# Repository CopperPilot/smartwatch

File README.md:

# CopperPilot Rugged Smartwatch

**A rugged 49 mm smartwatch around an ESP32-S3 module, with a 1.9-inch IPS screen under flat cover glass, a rotary crown, side and action buttons, an optical heart-rate sensor in a domed back and magnetic rear charging, on a standard 49 mm sport band. Designed end to end by CopperPilot from three photos and a short prompt.**

> [!NOTE]
> **Designed by [CopperPilot](https://copperpilot.ai).** CopperPilot's agents designed every board, schematic, layout and enclosure part in this repo from one prompt and a few reference photos, then checked them with the gates and reviews below. Nobody edited the design files by hand. The prompt asked for a rugged smartwatch like the one in three photos, with the same bands, buttons, crown and display size, and heart-rate tracking, plus a short list of decisions (band type, rear charging, crown and button mechanics, bonded cover glass, domed back). The owner then asked for two review findings on the charging input to be fixed; the agents chose the parts, drew and routed the board, modelled the case and fixed every review finding themselves. **It has not been fabricated, assembled or powered on yet.** Everything here is open for review: if you see something a senior engineer would flag, [open an issue](../../issues/new/choose).

One 34 x 40 mm, 2-layer, 1.0 mm board with parts on both sides inside a 45 x 49 x 15 mm case:
- **Front:** a 1.9-inch 170 x 320 IPS panel (ST7789V2, SPI) under a flat cover glass bonded onto a ledge inside a
  1.8 mm raised rim.
- **Sides:** a rotary crown (a cap pressed onto a horizontal-shaft encoder through a sealed bore) and a side button
  on the right, an action button on the left; both buttons press side-actuated switches and clip in.
- **Back:** a domed, RF-transparent rear cover with an optical window over the MAX30102 heart-rate sensor and a
  2-pin magnetic pogo receptacle for the charging cable.
- **Band:** a bought 49 mm sport band slides sideways into lug channels at the top and bottom of the case.

## Status

### Done

- [x] Schematic: KiCad ERC, 0 errors
- [x] Layout: KiCad DRC with schematic parity and zone refill, 0 errors, 0 unconnected
- [x] Board rules no looser than the fab's limits, nothing silenced
- [x] Every part on the footprint and 3D model of its exact LCSC part
- [x] Every placed part has a live, in-stock LCSC/JLCPCB part number
- [x] High-speed groups (USB, MIPI, DDR where present) routed, length-matched, on target impedance
- [x] Every user-facing connector opens towards its case opening (checked on its 3D model)
- [x] Every connector mates from a known side, with a keep-clear zone KiCad DRC enforces
- [x] Both ends of every board-to-board cable carry the same signal on each wire
- [x] Datasheet-level design review: 0 P0 and 0 P1 findings open on every board
- [x] Enclosure parts are closed solids that fit the product envelope
- [x] Every enclosure part is manufacturable by its process (wall thickness, build size)
- [x] Full assembly with the real PCBAs: no collisions, seated or along any insertion path
- [x] Every cable joins two real connectors and fits its route in every pose
- [x] Every connector faces what mates with it; every screw hole sits on a boss
- [x] Every port opening has its connector right behind it
- [x] Every button and control physically reaches the switch it works
- [x] Every camera's whole field of view clears the case
- [x] Every part is held by something real (screw, snap, clip, adhesive, press fit)
- [x] Gerbers, drill, BOM and CPL exist and agree with the PCB
- [x] Independent judge (compares renders to the reference photos): **8/10** ([notes](reviews/judge.md))

### Pending

- [ ] Gate `sourcing.bom` warn: 32 extended parts (each adds a JLCPCB feeder fee); prefer basic parts where equivalent
- [ ] Gate `kicad.drc` warn: DRC warning silk_over_copper x23
- [ ] **Not built.** The board has not been fabricated or assembled and no case has been machined or printed.
- [ ] **No firmware.** The ESP32-S3 firmware (display, crown, buttons, heart rate, charging status) is not written or tested.
- [ ] **Bought parts are specified from drawings.** The 1.9-inch panel, the 220 mAh battery, the magnetic charging cable and the 49 mm band are modelled from typical listing drawings; exact suppliers still have to be chosen and checked against those models.
- [ ] **Judge notes (8/10):** the band lug channels are cut into flat end walls instead of blending into angled lug chamfers; the rectangular panel leaves a slightly wider black border than the reference display; the grille next to the action button is cosmetic (8 holes, no speaker on the board).
- [ ] **Water resistance not designed or tested.** The crown bore, button bores and bonded glass are sealed by design intent only; no gaskets are specified or rated.
- [ ] **DRC warnings:** 32 cosmetic warnings (silkscreen over copper or overlapping, and seven footprints that differ from their library copy); 0 errors.

0 P0 · 0 P1 · 0 P2 review findings open; the full reviews with evidence and suggested fixes are in [reviews/](reviews). Every P0 and P1 the reviews raised was fixed before release.

## Build film

[docs/build-film.mp4](docs/build-film.mp4) (48 s, 720p). Every part backs out along the direction it was fitted and goes back in assembly order, and every cable is drawn along its real route. Every frame is replayed against the 3D models (no part passes through another, the camera stays outside, the product stays in frame and faces you, no flicker), and a separate critic watches the film ([notes](reviews/film.md)).

## Renders

| | |
|:---:|:---:|
| <br>*Three-quarter view* | <br>*Front* |
| <br>*Rear* | <br>*Left side* |
| <br>*Right side* | <br>*Exploded* |
| <br>*Inside, top cover lifted away, every cable* | <br>*Inside from below, bottom cover lifted away* |
| <br>*Ports* | <br>*Buttons and controls, next to the parts they press* |

## What's inside

**Brain:** ESP32-S3-MINI-1 (Wi-Fi + Bluetooth LE, 8 MB flash) with a 32.768 kHz RTC crystal; its antenna sits
behind the non-metal rear cover.
**Power path:** magnetic pogo input → TVS clamp → 0.5 A hold / 1.0 A trip resettable fuse → reverse-polarity P-FET →
36 V overvoltage switch (ETA7014) → 6.5 V-rated current-limited, reverse-blocking switch (TPS2553) → MCP73832
charger for a 220 mAh 1S LiPo, with load sharing to the system rail. A TPS63031 buck-boost makes 3.3 V, an LDO makes
1.8 V for the heart-rate sensor, and a two-channel driver dims the backlight. A push-button reset controller resets
the MCU when the side button is held.

| Board | Size | Layers | Parts | Tracks | Vias | KiCad project | Review |
|---|---|---|---|---|---|---|---|
| Main board | 34 × 40 mm | 2 | 120 | 1,522 | 151 | [`hardware/rugged-smartwatch.kicad_pro`](hardware/rugged-smartwatch.kicad_pro) | [0 P0 · 0 P1](reviews/review-main.md) |

**Bought parts** (modelled from their drawings; the assembly checks use these models):

- **Display panel**: 1.9-inch 170x320 IPS TFT LCD display module with ST7789V2 4-wire SPI interface and 12-pin 0.5 mm pitch FPC tail (separate LEDA/LEDK backlight pins)
- **Battery**: 3.7 V 220 mAh 1S LiPo pouch battery (352022) with integrated protection PCB and 2-pin 1.0 mm JST-SH lead
- **Display psa**: Die-cut perimeter acrylic pressure-sensitive adhesive gasket bonding front cover glass to case ledge

## How it was made

CopperPilot's agents worked from the prompt in [reference/prompt.md](reference/prompt.md) and 3 reference photos ([reference/](reference)). The pipeline scopes the product into a written contract ([design/spec.yaml](design/spec.yaml)), designs the boards and the enclosure in parallel, integrates them, and only moves on when the gates pass. A separate review agent reads every board against the part datasheets, and a separate judge compares the result with the photos.

- Pipeline wall clock: about **37 h** over 10 launches (pipeline v98 to v127).

**Reference vs build:**

<sub>Reference photos of a commercial product, used here only for comparison. All rights belong to their owners; this project is not affiliated with or endorsed by the product's maker.</sub>

## Repository layout

```
hardware/          KiCad 10 projects (main board at the top, daughter boards in their own folders)
  lcsc.*, rea_refs.*   symbols, footprints and 3D models for every part, so the project opens anywhere
case/out/          enclosure parts (STL)
case/purchased/    bought parts used in the assembly checks
case/generate_case.py  the parametric enclosure source (uses CopperPilot's CAD helpers, not yet public)
fab/               Gerbers, drill, BOM, CPL, schematic PDF and STEP for each board; fab/mech/ enclosure STEP/STL
design/spec.yaml   the design contract the agents wrote and the gates check
reviews/           gate report, design reviews, the judge's notes, KiCad ERC/DRC
reference/         the prompt and the reference photos
docs/              build film and renders
```

## Manufacture

Every board targets **JLCPCB** standard PCB + assembly (1.0 mm FR-4); every part has an LCSC number. Per board: upload `*-gerbers.zip`, then `*-bom.csv` and `*-cpl.csv` for assembly, and check the part rotations in JLCPCB's preview before ordering.

The case body, crown cap, buttons and sensor window are designed for CNC (6061 aluminium, acrylic or sapphire for
the window), the rear cover for SLA in a ceramic-filled resin so the radio can see out; STEP files for each part are
in `fab/mech/`, with STLs for test prints. The board is set up for JLCPCB fabrication and two-sided assembly
(Gerbers, BOM and CPL).

> [!WARNING]
> This design has not been built yet. Fix or accept the open review findings above before you order boards, and expect a first revision to need changes.

## Review this design

Hardware gets better with more eyes on it. We'd like to hear what you'd flag:

- **Open an issue** ([design review template](../../issues/new/choose)) for a wrong pin, a missing part, a tight clearance, a part you'd swap, or a P1 above you disagree with.
- **Send a pull request** with a fix. Say which board and which reference designators it touches.
- **Build one** and tell us how it went: photos, bring-up notes and failures are all welcome.

Start with [reviews/](reviews): every finding has its evidence and a suggested fix.

## License

[CERN-OHL-S-2.0](LICENSE). You may use, study, modify, make and sell products from this design; modified versions must be shared under the same licence.

Part and product names are used only to say what fits; all trademarks belong to their owners.

<p align="center"><a href="https://copperpilot.ai"><b>Designed by CopperPilot</b></a>: we accelerate hardware design.<br><sub>More open designs: <a href="https://github.com/CopperPilot">github.com/CopperPilot</a></sub></p>

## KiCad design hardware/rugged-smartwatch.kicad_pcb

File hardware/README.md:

# Rugged 49 mm Smartwatch — Hardware & Electrical Design Documentation

Generated from `rea/spec.yaml` by `rea-hardware` (JLCPCB 2-layer stackup, 34.0 x 40.0 mm board outline at origin with 6.0 mm corner radius, and 4x M1.6 mounting holes), and completed with verified LCSC components, symbols, footprints, and 3D models.

## 1. Power Tree, Protection & Quiescent Current Budget

- **Rear Magnetic Pogo Charging Input (`J3`, `YZT0755-20028-02025-01`, LCSC `C5280828`, plus `TP9` on `/VCHG_RAW`):**
  - **Contact Current Rating:** Rated `2.0 A` per contact (`2 contacts` = `VCHG_RAW` and `GND`). Peak charging current is `147 mA` (`0.07x` rated current, `>13x` safety margin).
  - **ESD, Negative-Transient Clamping, Overcurrent PPTC Fuse, Reverse-Polarity Blocking, Overvoltage Protection & Reverse-Current Blocking:**
    - `D2` (`ESDLC12VLB`, YANGJIE 12 V bidirectional ESD/surge protection TVS diode in DFN1006-2L, LCSC `C20168169`, `V_RWM = 12 V`, `V_BR = 14.0 V` min, `V_C = 20 V` at `I_PP = 6 A` `< 24 V`, connected between `/VCHG_RAW` and `/GND`) provides IEC 61000-4-2 +/-30 kV bidirectional ESD and surge clamping. Because `V_C <= 20 V`, negative ESD or reverse-polarity transients on `J3.1` are clamped to `>= -20 V` (well inside upstream P-MOSFET `Q7` `AO3401A` `V_DS(max) = -30 V` when `Q7` is off and `C24` holds `VCHG_IN` at `0 V`), while positive transients are clamped to `<= +20 V` so `U6.1` (`OVP_FB`, via `R27 = 35.7 kOhm` / `R28 = 10.0 kOhm`) never exceeds `20 V * 10.0 / 45.7 = 4.38 V` (strictly below `U6`'s `+6.0 V` FB Absolute Maximum Rating). `R26` (`100 kOhm`) bleeds `VCHG_RAW` to `0.00 V` when unmated so exterior gold-plated contacts never carry DC bias against skin.
    - `F2` (`0603L050SLYR`, Littelfuse `0.50 A` hold / `1.00 A` trip ultra-low-resistance `0.14 Ohm` typ / `0.35 Ohm` max 0603 PPTC resettable fuse, LCSC `C207014`) sits in series with `J3.1` between `/VCHG_RAW` (`F2.1`) and `/VCHG_FUSED` (`F2.2`), tripping at `<= 1.00 A` (`>3.4x` margin above the `147 mA` normal charge current and `< 52 mV` voltage drop at `147 mA`) to protect `D1` (`PMEG2010EA,115`, `1.0 A` max) and `U8` (`TPS2553DBVR`, `1.5 A` max).
    - `Q7` (`AO3401A`, P-MOSFET in SOT-23, LCSC `C15127`, `V_DS(max) = -30 V`, `V_GS(max) = +/-12 V`, `R_DS(on) ~ 50 mOhm`, drain `Q7.3` on `/VCHG_FUSED`, source `Q7.2` on `/VCHG_IN`, gate `Q7.1` on `/VCHG_Q7_G`) blocks reverse-polarity connections on `J3` before they can reach `U6`'s `-0.3 V` substrate limit. `Q7`'s gate is pulled to `GND` by `R38 = 100 kOhm` (`0402WGF1003TCE`, LCSC `C25741`, providing full `V_GS = -5 V` gate drive during normal 5 V charging and dissipating `< 4 mW` at 20 V clamping) and clamped across Source-to-Gate by `D11` (`PESD5V0S1BL`, LCSC `C2912556`).
    - `C24` (`GRM188R6YA106MA73D`, 10 uF 35 V X5R 0603, LCSC `C194427`) provides high-voltage input decoupling on `/VCHG_IN` per `ETA7014S2G` datasheet recommendations.
    - `U6` (`ETA7014S2G`, 36 V input overvoltage protection load switch in SOT-23-6, LCSC `C7465500`, `R_ON = 35 mOhm` typ) sits on `/VCHG_IN` (`U6.4`, with `VCC`/`EN` `U6.5`/`U6.2` filtered via `R29 = 1 kOhm` `0402WGF1001TCE`, LCSC `C11702` + `C23 = 1 uF` 50 V X5R 0402 `GRM155R61H105KE05D`, LCSC `C1518208`) and outputs `/VCHG_PROT` (`U6.3`, bypassed by `C26 = 1 uF` 25 V X5R 0402 `CL05A105KA5NQNC`, LCSC `C52923`). Precision `0.1%` thin-film divider `R27 = 35.7 kOhm` (`ERA-2AEB3572X`, LCSC `C2075580`) and `R28 = 10.0 kOhm` (`RT0402BRD0710KL`, LCSC `C190095`) on `OVP_FB` (`U6.1`, `V_FB = 1.26 V +/- 0.05 V` = `1.21 V` min to `1.31 V` max) programs the overvoltage cutoff threshold to `V_OVP(typ) = 1.26 V * (35.7 + 10.0) / 10.0 = 5.758 V`, with worst-case minimum `V_OVP(min) = 1.21 V * (35.7 * 0.999 + 10.0 * 1.001) / (10.0 * 1.001) = 5.521 V > 5.500 V` (guaranteeing normal `4.75–5.50 V` USB `vSafe5V` input never trips OVP) and worst-case maximum `V_OVP(max) = 1.31 V * (35.7 * 1.001 + 10.0 * 0.999) / (10.0 * 0.999) = 5.996 V < 6.000 V` (strictly below the `6.5 V` recommended operating and `7.0 V` Absolute Maximum Rating of downstream `U8` `TPS2553DBVR`, and below the `6.0 V` recommended operating and `7.0 V` Absolute Maximum Rating of `U2` `MCP73832T-2ACI/OT`), while `U6`'s internal soft-start controls capacitive hot-plug inrush into `C26` (`1 uF`) and `C11` (`4.7 uF`).
    - `U8` (`TPS2553DBVR`, TI `2.5–6.5 V` recommended operating / `7.0 V` Absolute Maximum Rating, `1.5 A`, `85 mOhm` current-limited power-distribution switch with active reverse input-output voltage blocking in SOT-23-6, LCSC `C55266`) sits downstream of `U6` between `/VCHG_PROT` (`IN` Pin 1, tied to `EN` Pin 3) and `/VBUS` (`OUT` Pin 6, decoupled by `C11 = 4.7 uF`), providing `504 mV` of recommended-operating margin (`6.500 V` vs `V_OVP(max) = 5.996 V`) and `1.004 V` of absolute-maximum margin (`7.000 V` vs `5.996 V`) across `U6`'s entire OVP tolerance window, active reverse-voltage/reverse-current blocking (`I_rev = 0.01 uA` typ / `1.0 uA` max when `V_OUT > V_IN + 135 mV`) so no battery voltage back-feeds onto `/VCHG_PROT` or exposed pogo contact `J3.1`, and `2 us` fast electronic current limiting programmed via `R41 = 35.7 kOhm` `0.1%` (`ERA-2AEB3572X`, LCSC `C2075580`) on `ILIM` (Pin 5, net `/VCHG_ILIM`) to `I_OS(min) = 667 mA`, `I_OS(typ) = 729 mA`, `I_OS(max) = 799 mA < 1.0 A`.
    - Factory charging test pad `TP9` (`B.Cu`) is connected to `/VCHG_RAW` upstream of `F2`, `Q7`, `U6`, and `U8` so factory fixture supplies pass through full overcurrent, reverse-polarity, OVP, soft-start, and RCB protection.
- **Battery Connector (`J2`, `SM02B-SRSS-TB(LF)(SN)`, LCSC `C160402`), 12 V PPTC Fuse (`F1`) & UVLO-Wakeable Reverse-Battery Protection (`Q2` + `Q6` + `Q8` + `D10` + `D13` + `D12` + `R34..R37`):**
  - Connector entry `/VBAT_IN` (`J2.1`) is protected directly at the connector by `D9` (`PESD5V0S1BL`, 5 V bidirectional TVS diode, LCSC `C2912556`) and series resettable PPTC fuse `F1` (`ASMD0603SL100-12V`, 12 V, `1.0 A` hold / `2.0 A` trip ultra-low-resistance `45 mOhm` typ 0603 PPTC fuse, LCSC `C48783158`).
  - High-side reverse-polarity P-MOSFET `Q2` (`AO3401A`, LCSC `C15127`, drain on `/VBAT_FUSED`, source on `/VBAT`) has its gate (`/VBAT_Q2_G`) pulled to its source (`/VBAT`) via `R34 = 1 MOhm` (`0402WGF1004TCE`, LCSC `C26083`) and pulled to `/GND` by N-MOSFET `Q6` (`BSS138K`, LCSC `C5224263`, `V_GS(th) = 0.4–1.0 V`), whose gate (`/VBAT_Q2_EN`) is driven from `/VBAT_FUSED` via `R35 = 100 kOhm` (`0402WGF1003TCE`, LCSC `C25741`) and from `/VBUS` via ultra-low-leakage diode `D10` (`1N4148WS`, LCSC `C2128`, net `/VBAT_WAKE`) in series with `R36 = 100 kOhm` (`0402WGF1003TCE`, LCSC `C25741`), while a second blocking diode `D13` (`1N4148WS`, LCSC `C2128`, net `/VBAT_SENSE_WAKE`) separately feeds `R37 = 100 kOhm` (`0402WGF1003TCE`, LCSC `C25741`), NPN BJT `Q8` (`MMBT3904`, LCSC `C909754`), and Schottky diode `D12` (`1N5819WS`, LCSC `C191023`) for reverse-polarity lockout without bleeding battery current (`0 uA` parasitic path from `VBAT_FUSED` through `R35 -> R36` when unplugged, preserving full `V_GS(Q6) = 3.0–4.2 V` gate drive).
- **1S LiPo Linear Charger (`U2`, `MCP73832T-2ACI/OT`, LCSC `C38066`) & Digital VBUS Detection (`R24`/`R25`):**
  - `R10 = 6.8 kOhm` (`C25917`) programs `I_REG = 1000 V / 6.8 kOhm = 147.1 mA` (`0.67C` for the `220 mAh` `LP352022` pouch cell).
  - Open-drain charge status output `U2.1` (`STAT`) is pulled up to `+3V3` via `R23` (`10 kOhm`) and routed to `U1.14` (`IO10`, `CHG_STAT`).
  - `/VBUS` presence is sensed digitally on `U1.15` (`GPIO11` / `RTC_GPIO11`) via `R24 = 68 kOhm` (`0402WGF6802TCE`, `C36871`) and `R25 = 100 kOhm` (`0402WGF1003TCE`, `C25741`), yielding `2.77–3.15 V > V_IH(min) = 2.475 V`.
- **Load-Sharing Power Path (`Q1` `AO3401A` + `D1` `PMEG2010EA,115` + `R13` `1 kOhm`), Buck-Boost +3V3 Regulation (`U4` `TPS63031DSKR` + `L1` `1.5 uH`) & LDO +1V8 Regulation (`U5` `ME6211C18M5G-N`):**
  - Low-leakage MEGA Schottky `D1` (`PMEG2010EA,115`, LCSC `C193668`) and P-MOSFET `Q1` (`AO3401A`, LCSC `C15127`, with `1 kOhm` gate pulldown `R13`) provide automatic single-diode-drop power path switching onto `/VSYS` (`10 uF` `C7`).
  - `U4` (`TPS63031DSKR`, LCSC `C15516`, `1.8–5.5 V` input, `3.3 V` fixed output buck-boost converter with `1.5 uH` inductor `L1` `WPN201610U1R5MT`, LCSC `C97017`, `EN` and `PS/SYNC` `U4.6`/`U4.7` tied to `VINA`/`VIN` on `/VSYS`, dedicated `100 nF` `C28` on `VINA` `U4.8`, `100 nF` `C3` adjacent to `U4.1` `VOUT`, and two parallel `10 uF` 25 V X5R 0603 bulk capacitors `C8` + `C27` `CL10A106MA8NRNC` `C96446` providing `>= 12 uF` DC-biased effective output capacitance) maintains regulated `+3V3` across the full `3.0–4.2 V` 1S LiPo discharge range, and `U5` (`ME6211C18M5G-N`, `C236671`, `1.8 V / 300 mA` LDO, `CE` tied to `VSYS`) supplies continuous `+1V8` to `U3` (`MAX30102EFD+T` `VDD`).
  - **Local IC Decoupling on `/+3V3`:** `C1` (`100 nF` 0402, `C1525`, at `8.29, 3.85 mm`) and `C13` (`10 uF` 0603, `C96446`, at `8.38, 5.85 mm`) are functionally grouped in the schematic and placed within `1.54–1.97 mm` of `U1` pin 3 (`3V3` pad at `10.02, 4.75 mm`) on `F.Cu` with dedicated local `/GND` stitching vias (`7.20, 3.85 mm` and `7.20, 6.625 mm`); `C4` (`100 nF` 0402, `C1525`, at `30.10, 23.45 mm`) is functionally grouped and placed immediately adjacent (`0.77 mm`) to `U9` (`TPS3421EGDRYR` at `31.25, 23.80 mm`) pin 4 (`VCC` pad at `30.86, 23.30 mm`) with a dedicated `/GND` stitching via at `(29.65, 23.65 mm)`.

## 2. Display Backlight Constant-Current Driver, UI Protection & Sensor Level Shifting

- **Display FPC (`J1`, `FPC-05FB-12PH20`, LCSC `C2856829`) & Constant-Current Backlight Driver (`U7`, `CAT4002ASD-GT3`, LCSC `C890382`):**
  - 12-pin 0.5 mm pitch double-sided contact FPC connector `J1` mates with the 12-pin 1.9-inch `170x320` `ST7789V2` IPS TFT module (`ZJY190S0800TG01` / `GMT169-01`), with `100 kOhm` pull-ups `R39`/`R40` on `LCD_CS`/`LCD_RES`, separate `LEDA` (Pin 3, tied to `/VSYS` with `1 uF` bypass `C25`), and `LEDK` (Pin 2, `/LCD_LEDK`) regulated by `U7` (`CAT4002ASD-GT3`, `R14 = 3.6 kOhm` for `41.7 mA` total sink current, dimmed via 1-wire EZDim pulse bursts on `U7.1` from `U1.25`).
- **Sealed-Enclosure Long-Press Push-Button Hardware Reset Supervisor (`U9`, `TPS3421EGDRYR`, LCSC `C2067262`):**
  - `U9` (`TPS3421EGDRYR`, `250 nA` push-button reset controller in SON-6, `TS` tied to `/GND` for `7.5 s` setup delay) monitors `SW2` (`/BTN_SIDE_SW`) and asserts a `400 ms` active-low hardware reset pulse on `/MCU_EN` (`U1.45`) when `SW2` is held for `>= 7.5 s`.
- **Rotary Encoder (`SW1`, `EC05E1220203`) & Tactile Button (`SW2`/`SW3`, `SKRTLAE010`) Contact-Current & ESD Protection:**
  - Switch terminals have `10 kOhm` pull-ups `R3..R6` to `+3V3` and 5 V bidirectional ESD TVS diodes `D5..D8` (`PESD5V0S1BL`, LCSC `C2912556`), followed by `10 kOhm` series current-limiting/ESD-isolation resistors `R30..R33` feeding `10 nF` encoder filter capacitors `C17..C18` (`<= 0.33 mA` contact discharge current) and `100 nF` tactile switch debounce capacitors `C19..C20`.
- **1.8 V <-> 3.3 V Fast-Mode I2C & Interrupt Level Translation (`Q3..Q5`, `BSS138K`, LCSC `C5224263`):**
  - `Q3`, `Q4`, and `Q5` use low-capacitance sub-1V-threshold small-signal N-MOSFETs (`BSS138K`, `C_iss = 25 pF`, `C_oss = 9.7 pF`, `C_rss = 2.2 pF`, `V_GS(th) = 0.4–1.0 V`) with gates on `+1V8`, `1.8 kOhm` pull-ups `R7, R8` (to `+1V8`) and `R20, R21` (to `+3V3`, `0402WGF1801TCE`, LCSC `C25871`) on `I2C_SCL` and `I2C_SDA` (yielding RC rise time `t_r ~ 70 ns << 300 ns` 400 kHz Fast-Mode limit while keeping total low-level sink current `I_OL = 2.83 mA < 3.0 mA`), and `10 kOhm` pull-ups `R9` (to `+1V8`) and `R22` (to `+3V3`, `0402WGF1002TCE`, LCSC `C25744`) on open-drain interrupt `HR_INT`.

## 3. Datasheet Derating Summary (Capacitors, MOSFETs, Connectors & Bootloader Path)

- **Capacitor Voltage Ratings (`>= 1.5x` Maximum Net Voltage):**
  - `/OVP_VCC` (`<= 20 V` surge clamped by `D2`): `C23` (`1 uF`, `GRM155R61H105KE05D`, `C1518208`) rated `50 V` (`2.50x` surge / `10.0x` nominal 5 V).
  - `/VCHG_IN` (`<= 20 V` surge clamped by `D2`): `C24` (`10 uF`, `GRM188R6YA106MA73D`, `C194427`) rated `35 V` (`1.75x` surge / `7.0x` nominal 5 V).
  - `/VCHG_PROT` (`<= 5.996 V` `U6` OVP cutoff): `C26` (`1 uF`, `CL05A105KA5NQNC`, `C52923`) rated `25 V` (`4.17x`).
  - `/VBUS` (`<= 5.996 V` OVP cutoff): `C11` (`4.7 uF`, `CL10A475KO8NNNC`, `C19666`) rated `16 V` (`2.67x`).
  - `/VBAT` (`<= 4.20 V` LiPo charge voltage): `C12` (`4.7 uF`, `CL10A475KO8NNNC`, `C19666`) rated `16 V` (`3.81x`).
  - `/VSYS` (`<= 5.8 V` OVP / `4.6 V` nominal): `C7, C14` (`10 uF`, `25 V`, `C96446`), `C25` (`1 uF`, `25 V`, `C52923`), and `C6, C28` (`100 nF`, `16 V`, `C1525`) provide `>= 2.76x` margin.
  - `/+3V3`, `/+1V8`, `/VBAT_ADC`, `/MCU_EN`, UI & RTC crystal nets (`<= 3.3 V`): `C1..C5, C15, C19, C20` (`16 V`), `C8, C9, C10, C13, C27` (`25 V`), and `C17, C18, C21, C22` (`50 V`) provide `>= 4.85x` margin.
- **MOSFET `|V_GS|` and `|V_DS|` Ratings:**
  - `Q7` (`AO3401A`, `V_DS(max) = -30 V`, `V_GS(max) = +/-12 V`): upstream `D2` (`ESDLC12VLB`, `V_C = 20 V` at `6 A`) clamps `|V_DS| <= 20 V < 30 V`, and `D11` (`PESD5V0S1BL` across Source-to-Gate) clamps `|V_GS| <= 7.0 V < 12 V`.
  - `Q1, Q2` (`AO3401A`, `V_DS(max) = -30 V`, `V_GS(max) = +/-12 V`): operate on `/VBUS` (`<= 6.0 V`) and `/VBAT` (`<= 4.2 V`), keeping `|V_GS| <= 6.0 V < 12 V` and `|V_DS| <= 6.0 V < 30 V`.
  - `Q3..Q6` (`BSS138K`, `V_DS(max) = 60 V`, `V_GS(max) = +/-20 V`): operate on `1.8 V`, `3.3 V`, and `4.2 V` nets (`|V_GS| <= 4.2 V < 20 V`).
- **Connector Contact Current Ratings & Ground Returns:**
  - `J3` (`YZT0755-20028-02025-01`, 2-pin pogo): rated `2.0 A`/contact vs `147 mA` charge current (`13.6x` margin).
  - `J2` (`SM02B-SRSS-TB(LF)(SN)`, 2-pin JST-SH): rated `1.0 A`/contact vs `<= 365 mA` peak battery current (`2.74x` margin).
  - `J1` (`FPC-05FB-12PH20`, 12-pin 0.5 mm FPC): rated `0.5 A`/contact vs `41.7 mA` on `LEDA`/`LEDK` and `< 15 mA` on `+3V3` `VDD`, with 4 distributed `GND` return pins (`Pins 1, 5, 6, 12`) flanking the backlight and 4-wire SPI signals.
- **MCU Programming & Bootloader Conditions (`U1`, `ESP32-S3-MINI-1-N8`):**
  - Native USB Serial/JTAG (`GPIO19` `USB_D-` / `GPIO20` `USB_D+` via `22 Ohm` `R15`/`R16` and `PESD5V0U1BL` `D3`/`D4`) and `UART0` (`U0TXD`/`U0RXD`), `MCU_EN` (`R1 = 10 kOhm` pull-up to `+3V3`, `C10 = 1 uF` delay, `TP6`), `GPIO0` (`BOOT_IO0`, `R2 = 10 kOhm` pull-up to `+3V3`, `TP5`), `+3V3` (`TP8`), `VCHG_RAW` (`TP9`), and `GND` (`TP7`) are exposed on `B.Cu` pogo test pads `TP1..TP9` (`GPIO45` and `GPIO46` strapping pins left unconnected at default internal pull-down).

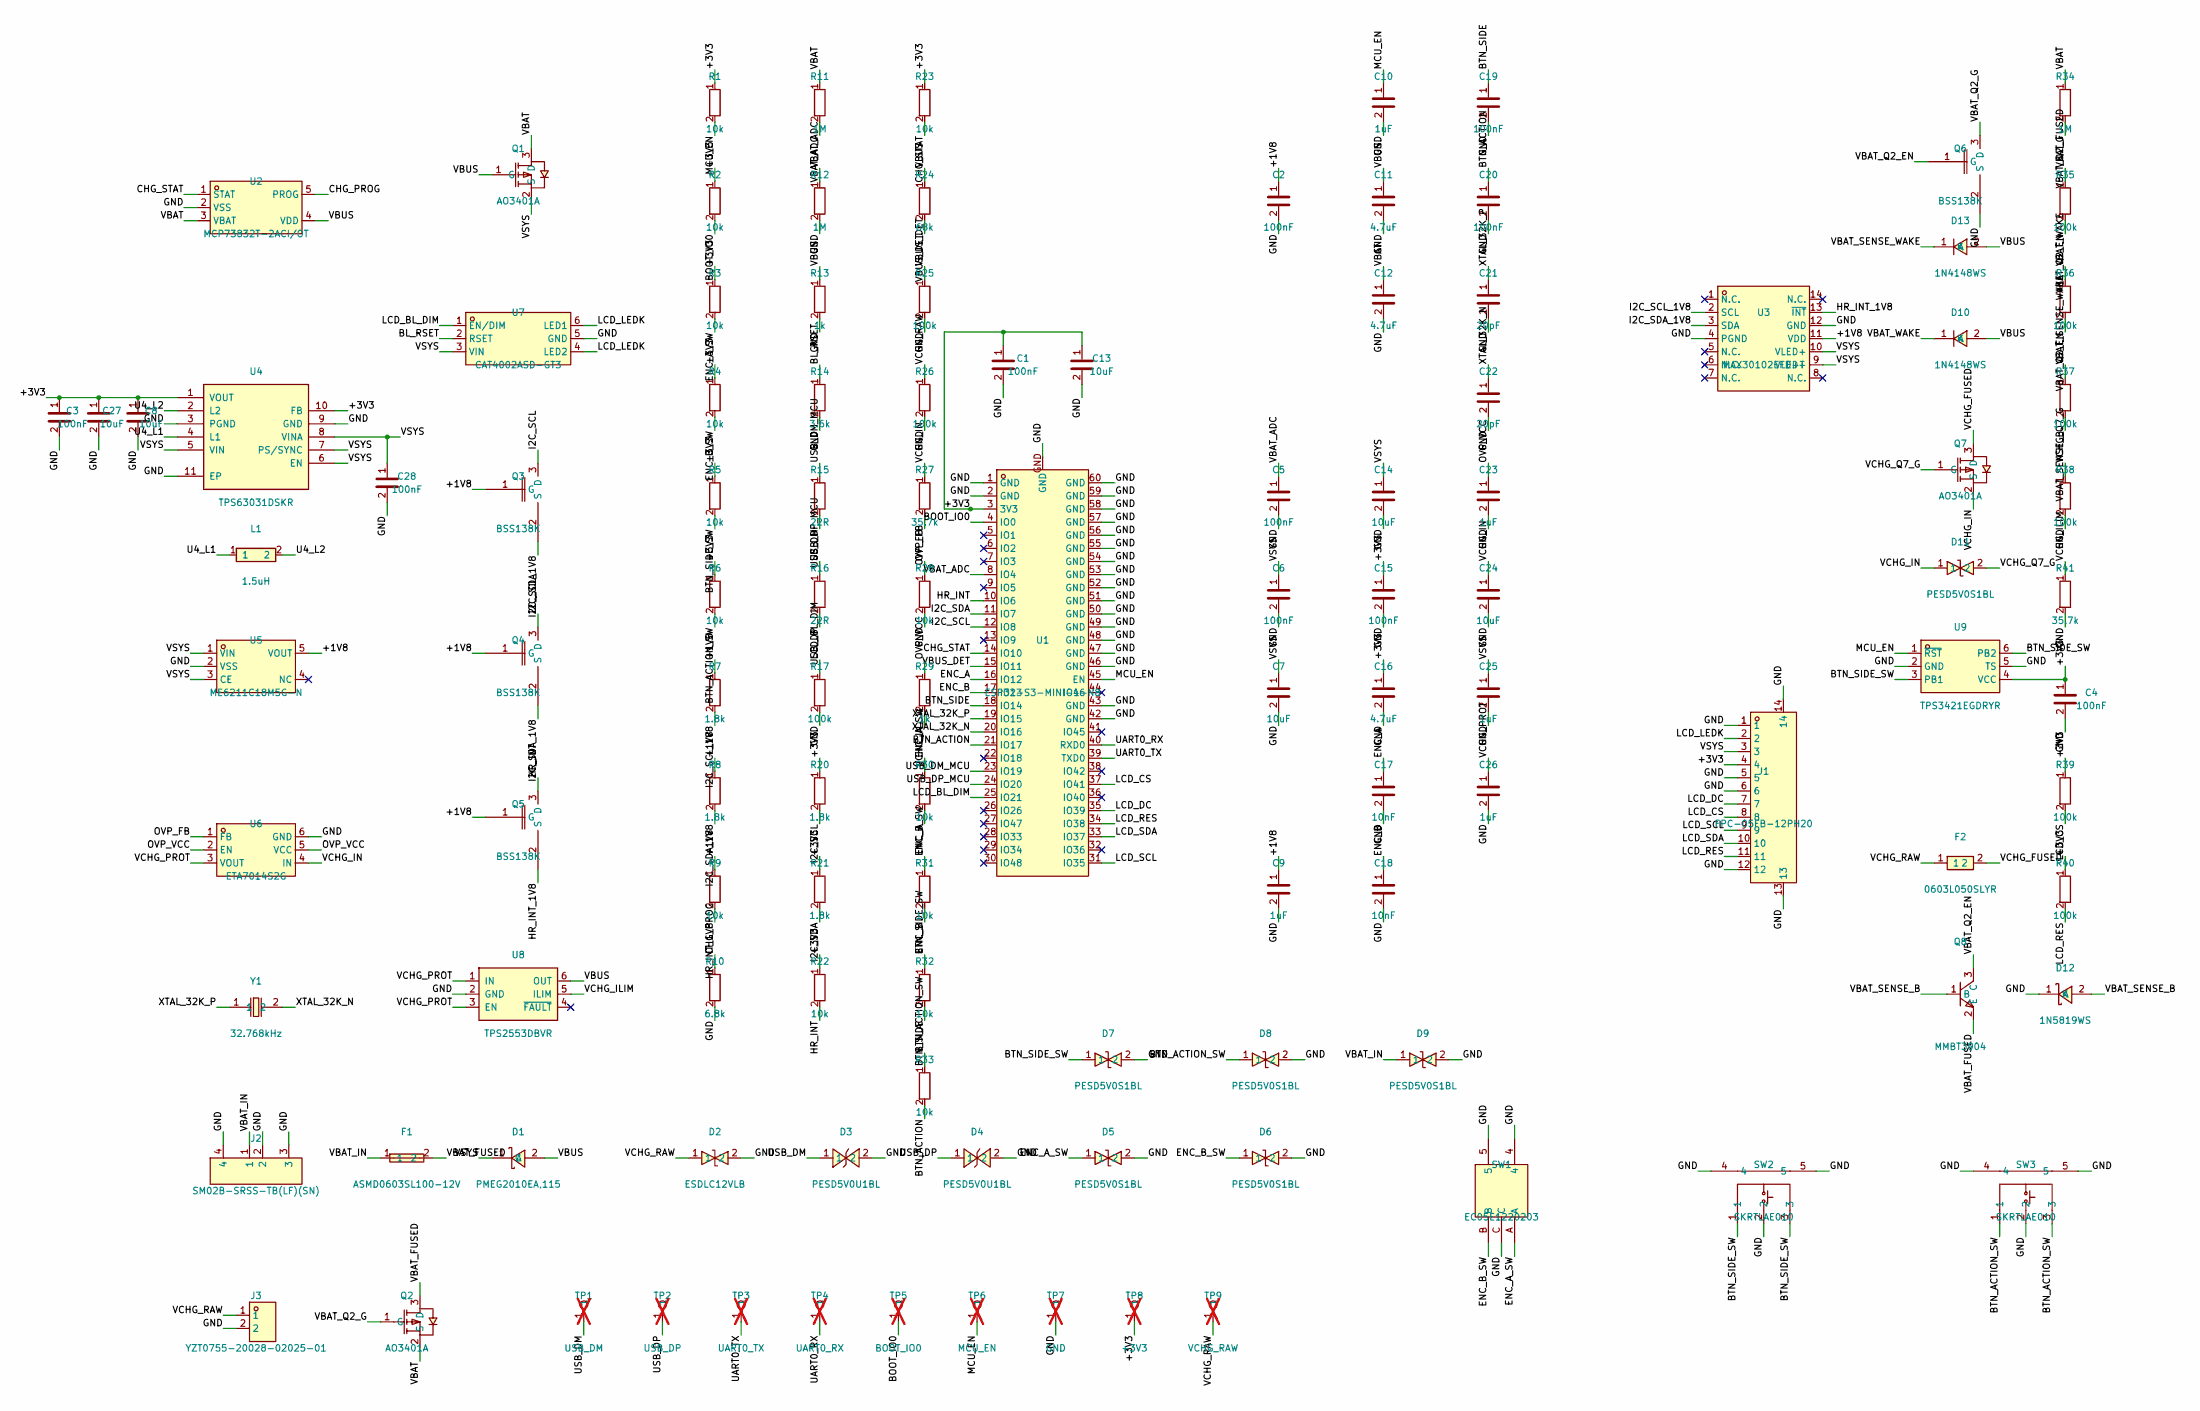
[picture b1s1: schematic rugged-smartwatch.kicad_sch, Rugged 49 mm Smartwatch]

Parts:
C1, C2, C3, C4, C5, C6, C15, C19, C20, C28: 100nF; C_0402_1005Metric; MPN CL05B104KO5NNNC; LCSC C1525
C7, C8, C13, C14, C27: 10uF; C_0603_1608Metric; MPN CL10A106MA8NRNC; LCSC C96446
C9, C10, C25, C26: 1uF; C_0402_1005Metric; MPN CL05A105KA5NQNC; LCSC C52923
C11, C12, C16: 4.7uF; C_0603_1608Metric; MPN CL10A475KO8NNNC; LCSC C19666
C17, C18: 10nF; C_0402_1005Metric; MPN CC0402KRX7R9BB103; LCSC C60133
C21, C22: 20pF; C_0402_1005Metric; MPN 0402CG200J500NT; LCSC C1554
C23: 1uF; C_0402_1005Metric; MPN GRM155R61H105KE05D; LCSC C1518208
C24: 10uF; C_0603_1608Metric; MPN GRM188R6YA106MA73D; LCSC C194427
D1: PMEG2010EA,115; SOD-323_L1.8-W1.3-LS2.5-RD; MPN PMEG2010EA,115; LCSC C193668
D2: ESDLC12VLB; DFN1006-2L-BI; MPN ESDLC12VLB; LCSC C20168169
D3, D4: PESD5V0U1BL; SOD-882_L1.0-W0.6-BI-1; MPN PESD5V0U1BL; LCSC C2827663
D5, D6, D7, D8, D9, D11: PESD5V0S1BL; DFN1006-2L-BI-1; MPN PESD5V0S1BL; LCSC C2912556
D10, D13: 1N4148WS; SOD-323_L1.8-W1.3-LS2.5-RD; MPN 1N4148WS; LCSC C2128
D12: 1N5819WS; SOD-323_L1.8-W1.3-LS2.5-RD; MPN 1N5819WS; LCSC C191023
F1: ASMD0603SL100-12V; F0603; MPN ASMD0603SL100-12V; LCSC C48783158
F2: 0603L050SLYR; F0603; MPN 0603L050SLYR; LCSC C207014
J1: FPC-05FB-12PH20; FPC-SMD_12P-P0.50_XUNPU_FPC-05FB-12PH20; MPN FPC-05FB-12PH20; LCSC C2856829
J2: SM02B-SRSS-TB(LF)(SN); CONN-SMD_2P-P1.00_SM02B-SRSS-TB-LF-SN; MPN SM02B-SRSS-TB(LF)(SN); LCSC C160402
J3: YZT0755-20028-02025-01; CONN-SMD_YZT0755-20028-02025-01; MPN YZT0755-20028-02025-01; LCSC C5280828
L1: 1.5uH; IND-SMD_L2.0-W1.6; MPN WPN201610U1R5MT; LCSC C97017
Q1, Q2, Q7: AO3401A; SOT-23_L2.9-W1.3-P1.90-LS2.4-BR; MPN AO3401A; LCSC C15127
Q3, Q4, Q5, Q6: BSS138K; SOT-23-3_L2.9-W1.3-P1.90-LS2.4-BR; MPN BSS138K; LCSC C5224263
Q8: MMBT3904; SOT-23-3_L2.9-W1.3-P1.90-LS2.4-BR; MPN MMBT3904; LCSC C909754
R1, R2, R3, R4, R5, R6, R9, R22, R23, R30, R31, R32, R33: 10k; R_0402_1005Metric; MPN 0402WGF1002TCE; LCSC C25744
R7, R8, R20, R21: 1.8k; R_0402_1005Metric; MPN 0402WGF1801TCE; LCSC C25871
R10: 6.8k; R_0402_1005Metric; MPN 0402WGF6801TCE; LCSC C25917
R11, R12, R34: 1M; R_0402_1005Metric; MPN 0402WGF1004TCE; LCSC C26083
R13, R29: 1k; R_0402_1005Metric; MPN 0402WGF1001TCE; LCSC C11702
R14: 3.6k; R_0402_1005Metric; MPN 0402WGF3601TCE; LCSC C25891
R15, R16: 22R; R_0402_1005Metric; MPN 0402WGF220JTCE; LCSC C25092
R17, R25, R26, R35, R36, R37, R38, R39, R40: 100k; R_0402_1005Metric; MPN 0402WGF1003TCE; LCSC C25741
R24: 68k; R_0402_1005Metric; MPN 0402WGF6802TCE; LCSC C36871
R27, R41: 35.7k; R_0402_1005Metric; MPN ERA-2AEB3572X; LCSC C2075580
R28: 10k; R_0402_1005Metric; MPN RT0402BRD0710KL; LCSC C190095
SW1: EC05E1220203; SW-SMD_EC05E1220203; MPN EC05E1220203; LCSC C390930
SW2, SW3: SKRTLAE010; KEY-SMD_SKRTLAE010; MPN SKRTLAE010; LCSC C110293
TP1: USB_DM; TestPoint_Pad_D1.0mm; not fitted
TP2: USB_DP; TestPoint_Pad_D1.0mm; not fitted
TP3: UART0_TX; TestPoint_Pad_D1.0mm; not fitted
TP4: UART0_RX; TestPoint_Pad_D1.0mm; not fitted
TP5: BOOT_IO0; TestPoint_Pad_D1.0mm; not fitted
TP6: MCU_EN; TestPoint_Pad_D1.0mm; not fitted
TP7: GND; TestPoint_Pad_D1.0mm; not fitted
TP8: +3V3; TestPoint_Pad_D1.0mm; not fitted
TP9: VCHG_RAW; TestPoint_Pad_D1.0mm; not fitted
U1: ESP32-S3-MINI-1-N8; BULETM-SMD_ESP32-S3-MINI-1-N8; MPN ESP32-S3-MINI-1-N8; LCSC C2913206
U2: MCP73832T-2ACI/OT; SOT-23-5_L3.0-W1.7-P0.95-LS2.8-BL; MPN MCP73832T-2ACI/OT; LCSC C38066
U3: MAX30102EFD+T; OESIP-14_L5.6-W3.3-P0.80-TL; MPN MAX30102EFD+T; LCSC C6454833
U4: TPS63031DSKR; SON-10_L2.5-W2.5-P0.50-TL-EP; MPN TPS63031DSKR; LCSC C15516
U5: ME6211C18M5G-N; SOT-23-5_L3.0-W1.7-P0.95-LS2.8-BR; MPN ME6211C18M5G-N; LCSC C236671
U6: ETA7014S2G; SOT-23-6_L2.9-W1.6-P0.95-LS2.8-BL; MPN ETA7014S2G; LCSC C7465500
U7: CAT4002ASD-GT3; SC-70-6_L2.0-W1.3-P0.65-LS2.1-BR; MPN CAT4002ASD-GT3; LCSC C890382
U8: TPS2553DBVR; SOT-23-6_L2.9-W1.6-P0.95-LS2.8-BR; MPN TPS2553DBVR; LCSC C55266
U9: TPS3421EGDRYR; SON-6_L1.5-W1.0-P0.50-BL; MPN TPS3421EGDRYR; LCSC C2067262
Y1: 32.768kHz; FC-135R_L3.2-W1.5; MPN Q13FC13500004; LCSC C32346

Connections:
/+1V8: C2.1, C9.1, Q3.1 (G), Q4.1 (G), Q5.1 (G), R7.1, R8.1, R9.1, U3.11 (VDD), U5.5 (VOUT)
/+3V3: C1.1, C3.1, C4.1, C8.1, C13.1, C15.1, C16.1, C27.1, J1.4, R1.1, R2.1, R3.1, R4.1, R5.1, R6.1, R20.1, R21.1, R22.1, R23.1, R39.1, R40.1, TP8.1, U1.3 (3V3), U4.1 (VOUT), U4.10 (FB), U9.4 (VCC)
/BL_RSET: R14.1, U7.2 (RSET)
/BOOT_IO0: R2.2, TP5.1, U1.4 (IO0)
/BTN_ACTION: C20.1, R33.2, U1.21 (IO17)
/BTN_ACTION_SW: D8.1, R6.2, R33.1, SW3.1, SW3.3
/BTN_SIDE: C19.1, R32.2, U1.18 (IO14)
/BTN_SIDE_SW: D7.1, R5.2, R32.1, SW2.1, SW2.3, U9.3 (PB1), U9.6 (PB2)
/CHG_PROG: R10.1, U2.5 (PROG)
/CHG_STAT: R23.2, U1.14 (IO10), U2.1 (STAT)
/ENC_A: C17.1, R30.2, U1.16 (IO12)
/ENC_A_SW: D5.1, R3.2, R30.1, SW1.A
/ENC_B: C18.1, R31.2, U1.17 (IO13)
/ENC_B_SW: D6.1, R4.2, R31.1, SW1.B
/GND: C1.2, C2.2, C3.2, C4.2, C5.2, C6.2, C7.2, C8.2, C9.2, C10.2, C11.2, C12.2, C13.2, C14.2, C15.2, C16.2, C17.2, C18.2, C19.2, C20.2, C21.2, C22.2, C23.2, C24.2, C25.2, C26.2, C27.2, C28.2, D2.2, D3.2, D4.2, D5.2, D6.2, D7.2, D8.2, D9.2, D12.1 (K), J1.1, J1.5, J1.6, J1.12, J1.13, J1.14, J2.2, J2.3, J2.4, J3.2, Q6.2 (S), R10.2, R12.2, R13.2, R14.2, R17.2, R25.2, R26.2, R28.2, R38.2, R41.2, SW1.4, SW1.5, SW1.C, SW2.2, SW2.4, SW2.5, SW3.2, SW3.4, SW3.5, TP7.1, U1.1 (GND), U1.2 (GND), U1.42 (GND), U1.43 (GND), U1.46 (GND), U1.47 (GND), U1.48 (GND), U1.49 (GND), U1.50 (GND), U1.51 (GND), U1.52 (GND), U1.53 (GND), U1.54 (GND), U1.55 (GND), U1.56 (GND), U1.57 (GND), U1.58 (GND), U1.59 (GND), U1.60 (GND), U1.GND, U2.2 (VSS), U3.4 (PGND), U3.12 (GND), U4.3 (PGND), U4.9 (GND), U4.11 (EP), U5.2 (VSS), U6.6 (GND), U7.5 (GND), U8.2 (GND), U9.2 (GND), U9.5 (TS)
/HR_INT: Q5.3 (D), R22.2, U1.10 (IO6)
/HR_INT_1V8: Q5.2 (S), R9.2, U3.13 (~INT)
/I2C_SCL: Q3.3 (D), R20.2, U1.12 (IO8)
/I2C_SCL_1V8: Q3.2 (S), R7.2, U3.2 (SCL)
/I2C_SDA: Q4.3 (D), R21.2, U1.11 (IO7)
/I2C_SDA_1V8: Q4.2 (S), R8.2, U3.3 (SDA)
/LCD_BL_DIM: R17.1, U1.25 (IO21), U7.1 (EN/DIM)
/LCD_CS: J1.8, R39.2, U1.37 (IO41)
/LCD_DC: J1.7, U1.35 (IO39)
/LCD_LEDK: J1.2, U7.4 (LED2), U7.6 (LED1)
/LCD_RES: J1.11, R40.2, U1.34 (IO38)
/LCD_SCL: J1.9, U1.31 (IO35)
/LCD_SDA: J1.10, U1.33 (IO37)
/MCU_EN: C10.1, R1.2, TP6.1, U1.45 (EN), U9.1 (~RST)
/OVP_FB: R27.2, R28.1, U6.1 (FB)
/OVP_VCC: C23.1, R29.1, U6.2 (EN), U6.5 (VCC)
/U4_L1: L1.1, U4.4 (L1)
/U4_L2: L1.2, U4.2 (L2)
/UART0_RX: TP4.1, U1.40 (RXD0)
/UART0_TX: TP3.1, U1.39 (TXD0)
/USB_DM: D3.1, R15.2, TP1.1
/USB_DM_MCU: R15.1, U1.23 (IO19)
/USB_DP: D4.1, R16.2, TP2.1
/USB_DP_MCU: R16.1, U1.24 (IO20)
/VBAT: C12.1, Q1.3 (D), Q2.2 (S), R11.1, R34.1, U2.3 (VBAT)
/VBAT_ADC: C5.1, R11.2, R12.1, U1.8 (IO4)
/VBAT_FUSED: F1.2, Q2.3 (D), Q8.2 (E), R35.1
/VBAT_IN: D9.1, F1.1, J2.1
/VBAT_Q2_EN: Q6.1 (G), Q8.3 (C), R35.2, R36.2
/VBAT_Q2_G: Q2.1 (G), Q6.3 (D), R34.2
/VBAT_SENSE_B: D12.2 (A), Q8.1 (B), R37.2
/VBAT_SENSE_WAKE: D13.1 (K), R37.1
/VBAT_WAKE: D10.1 (K), R36.1
/VBUS: C11.1, D1.2 (A), D10.2 (A), D13.2 (A), Q1.1 (G), R13.1, R24.1, U2.4 (VDD), U8.6 (OUT)
/VBUS_DET: R24.2, R25.1, U1.15 (IO11)
/VCHG_FUSED: F2.2, Q7.3 (D)
/VCHG_ILIM: R41.1, U8.5 (ILIM)
/VCHG_IN: C24.1, D11.1, Q7.2 (S), R27.1, R29.2, U6.4 (IN)
/VCHG_PROT: C26.1, U6.3 (VOUT), U8.1 (IN), U8.3 (EN)
/VCHG_Q7_G: D11.2, Q7.1 (G), R38.1
/VCHG_RAW: D2.1, F2.1, J3.1, R26.1, TP9.1
/VSYS: C6.1, C7.1, C14.1, C25.1, C28.1, D1.1 (C), J1.3, Q1.2 (S), U3.9 (VLED+), U3.10 (VLED+), U4.5 (VIN), U4.6 (EN), U4.7 (PS/SYNC), U4.8 (VINA), U5.1 (VIN), U5.3 (CE), U7.3 (VIN)
/XTAL_32K_N: C22.1, U1.20 (IO16), Y1.2
/XTAL_32K_P: C21.1, U1.19 (IO15), Y1.1

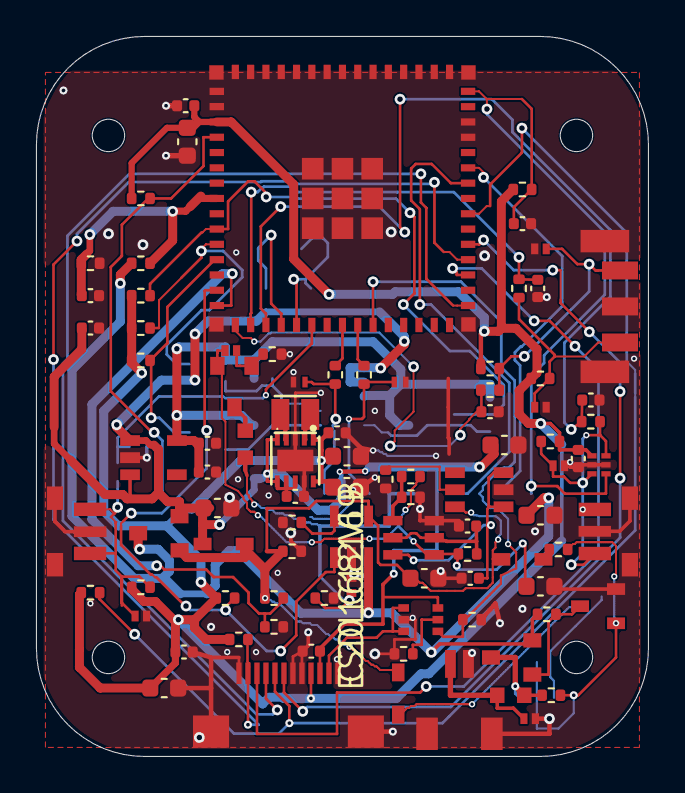
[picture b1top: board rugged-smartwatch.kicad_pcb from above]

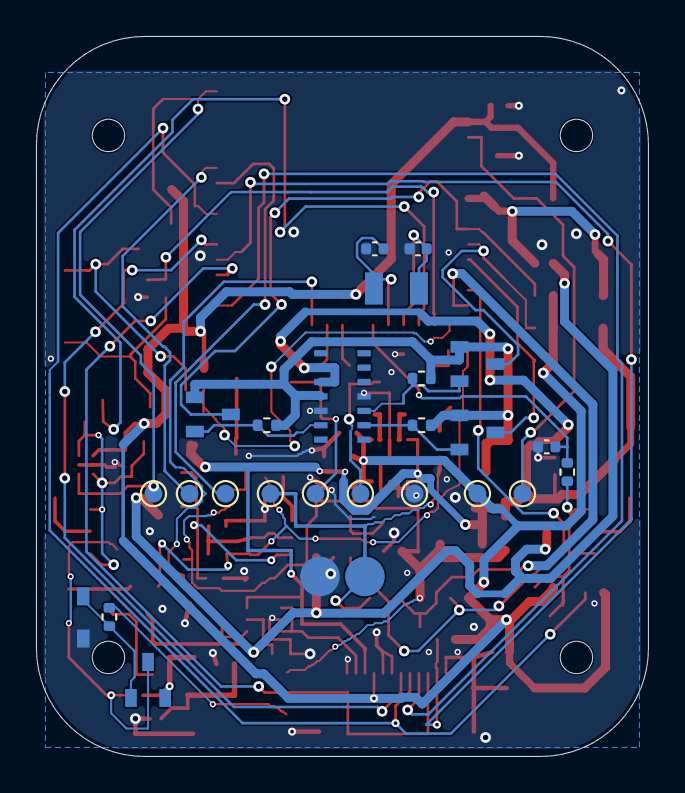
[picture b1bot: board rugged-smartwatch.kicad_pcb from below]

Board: 2 copper layers, 34.0 x 40.0 mm, 120 parts (25 on the bottom side), 59 nets.

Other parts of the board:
H1, H2, H3, H4: MountingHole; MountingHole_1.8mm

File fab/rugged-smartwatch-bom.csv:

Comment,Designator,Footprint,LCSC Part #
100nF,"C1,C2,C3,C4,C5,C6,C15,C19,C20,C28",C_0402_1005Metric,C1525
1uF,"C9,C10,C25,C26",C_0402_1005Metric,C52923
4.7uF,"C11,C12,C16",C_0603_1608Metric,C19666
10uF,"C7,C8,C13,C14,C27",C_0603_1608Metric,C96446
10nF,"C17,C18",C_0402_1005Metric,C60133
20pF,"C21,C22",C_0402_1005Metric,C1554
1uF,C23,C_0402_1005Metric,C1518208
10uF,C24,C_0603_1608Metric,C194427
"PMEG2010EA,115",D1,SOD-323_L1.8-W1.3-LS2.5-RD,C193668
1N4148WS,"D10,D13",SOD-323_L1.8-W1.3-LS2.5-RD,C2128
PESD5V0S1BL,"D5,D6,D7,D8,D9,D11",DFN1006-2L-BI-1,C2912556
1N5819WS,D12,SOD-323_L1.8-W1.3-LS2.5-RD,C191023
ESDLC12VLB,D2,DFN1006-2L-BI,C20168169
PESD5V0U1BL,"D3,D4",SOD-882_L1.0-W0.6-BI-1,C2827663
ASMD0603SL100-12V,F1,F0603,C48783158
0603L050SLYR,F2,F0603,C207014
FPC-05FB-12PH20,J1,FPC-SMD_12P-P0.50_XUNPU_FPC-05FB-12PH20,C2856829
SM02B-SRSS-TB(LF)(SN),J2,CONN-SMD_2P-P1.00_SM02B-SRSS-TB-LF-SN,C160402
YZT0755-20028-02025-01,J3,CONN-SMD_YZT0755-20028-02025-01,C5280828
1.5uH,L1,IND-SMD_L2.0-W1.6,C97017
AO3401A,"Q1,Q2,Q7",SOT-23_L2.9-W1.3-P1.90-LS2.4-BR,C15127
BSS138K,"Q3,Q4,Q5,Q6",SOT-23-3_L2.9-W1.3-P1.90-LS2.4-BR,C5224263
MMBT3904,Q8,SOT-23-3_L2.9-W1.3-P1.90-LS2.4-BR,C909754
10k,"R1,R2,R3,R4,R5,R6,R9,R22,R23,R30,R31,R32,R33",R_0402_1005Metric,C25744
6.8k,R10,R_0402_1005Metric,C25917
1M,"R11,R12,R34",R_0402_1005Metric,C26083
1k,"R13,R29",R_0402_1005Metric,C11702
3.6k,R14,R_0402_1005Metric,C25891
22R,"R15,R16",R_0402_1005Metric,C25092
100k,"R17,R25,R26,R35,R36,R37,R38,R39,R40",R_0402_1005Metric,C25741
1.8k,"R7,R8,R20,R21",R_0402_1005Metric,C25871
68k,R24,R_0402_1005Metric,C36871
35.7k,"R27,R41",R_0402_1005Metric,C2075580
10k,R28,R_0402_1005Metric,C190095
EC05E1220203,SW1,SW-SMD_EC05E1220203,C390930
SKRTLAE010,"SW2,SW3",KEY-SMD_SKRTLAE010,C110293
ESP32-S3-MINI-1-N8,U1,BULETM-SMD_ESP32-S3-MINI-1-N8,C2913206
MCP73832T-2ACI/OT,U2,SOT-23-5_L3.0-W1.7-P0.95-LS2.8-BL,C38066
MAX30102EFD+T,U3,OESIP-14_L5.6-W3.3-P0.80-TL,C6454833
TPS63031DSKR,U4,SON-10_L2.5-W2.5-P0.50-TL-EP,C15516
ME6211C18M5G-N,U5,SOT-23-5_L3.0-W1.7-P0.95-LS2.8-BR,C236671
ETA7014S2G,U6,SOT-23-6_L2.9-W1.6-P0.95-LS2.8-BL,C7465500
CAT4002ASD-GT3,U7,SC-70-6_L2.0-W1.3-P0.65-LS2.1-BR,C890382
TPS2553DBVR,U8,SOT-23-6_L2.9-W1.6-P0.95-LS2.8-BR,C55266
TPS3421EGDRYR,U9,SON-6_L1.5-W1.0-P0.50-BL,C2067262
32.768kHz,Y1,FC-135R_L3.2-W1.5,C32346

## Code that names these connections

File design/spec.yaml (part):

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  - {refs: [Y1], role: rtc_crystal_32k, mpn: Q13FC13500004, lcsc: C32346, footprint: "lcsc:FC-135R_L3.2-W1.5", description: "32.768 kHz 12.5 pF 20 ppm SMD3215-2P RTC crystal oscillator"}
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  - {refs: [Q8], role: revbat_lockout_npn, mpn: MMBT3904, lcsc: C909754, footprint: "lcsc:SOT-23-3_L2.9-W1.3-P1.90-LS2.4-BR", description: "40 V 200 mA NPN bipolar transistor clamping Q6 gate (VBAT_Q2_EN) to VBAT_FUSED during reverse-battery insertion while staying off at VBAT_FUSED >= 0 V"}
  - {refs: [D1], role: load_share_schottky, mpn: "PMEG2010EA,115", lcsc: C193668, footprint: "lcsc:SOD-323_L1.8-W1.3-LS2.5-RD", description: "20 V 1 A low-Vf low-leakage (10 uA typ at 5 V) MEGA Schottky barrier rectifier for VBUS -> VSYS power path"}
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  - {refs: [D12], role: revbat_sense_schottky, mpn: 1N5819WS, lcsc: C191023, footprint: "lcsc:SOD-323_L1.8-W1.3-LS2.5-RD", description: "40 V 1 A low-Vf Schottky diode clamping Q8 base (VBAT_SENSE_B) to ~0.22 V above GND so Q8 remains off at VBAT_FUSED = 0 V and saturates when VBAT_FUSED < -0.4 V"}
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  - {refs: [D3, D4], role: usb_esd_tvs, mpn: PESD5V0U1BL, lcsc: C2827663, footprint: "lcsc:SOD-882_L1.0-W0.6-BI-1", description: "Ultra-low-capacitance (0.6 pF) bidirectional ESD protection diode on USB D-/D+ lines"}
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  - {refs: [C17, C18], role: enc_filter_10n, mpn: CC0402KRX7R9BB103, lcsc: C60133, footprint: "Capacitor_SMD:C_0402_1005Metric", description: "10 nF 50 V X7R 0402 RC debounce filter capacitor for rotary encoder SW1 (with 10k R30/R31 limiting contact current to <= 0.33 mA)"}
  - {refs: [C9, C10, C25, C26], role: decouple_1u, mpn: CL05A105KA5NQNC, lcsc: C52923, footprint: "Capacitor_SMD:C_0402_1005Metric", description: "1 uF 25 V X5R 0402 +1V8 output bypass (C9), EN delay (C10), CAT4002A VIN/LEDA bypass (C25), and TPS2553DBVR IN bypass on VCHG_PROT (C26) capacitor"}
  - {refs: [C23], role: ovp_vcc_1u_50v, mpn: GRM155R61H105KE05D, lcsc: C1518208, footprint: "Capacitor_SMD:C_0402_1005Metric", description: "1 uF 50 V X5R 0402 high-voltage bypass capacitor for ETA7014S2G OVP_VCC pin"}
  - {refs: [C24], role: vchg_in_10u_35v, mpn: GRM188R6YA106MA73D, lcsc: C194427, footprint: "Capacitor_SMD:C_0603_1608Metric", description: "10 uF 35 V X5R 0603 high-voltage input decoupling capacitor on VCHG_IN per ETA7014S2G datasheet recommendation"}
  - {refs: [C11, C12, C16], role: bulk_4u7, mpn: CL10A475KO8NNNC, lcsc: C19666, footprint: "Capacitor_SMD:C_0603_1608Metric", description: "4.7 uF 16 V X5R 0603 charger, battery, and display FPC bulk capacitor"}
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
